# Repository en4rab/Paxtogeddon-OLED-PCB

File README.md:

# Paxtogeddon-OLED-PCB
### Hardware files for the Paxtogeddon reader with OLED display

### kicad

The kicad directory contains the kicad project files to make a PCB for the Paxtogeddon reader. This was a project to learn Kicad and PCB design so set your expectations accordingly! If you just want to make one Paxtogeddon reader to use then you might find using 00Waz's [protoboard design](https://github.com/00Waz/Paxtogeddon-Reader) quicker and easier than ordering pcb's and smt parts from China.

### gerbers

The gerbers directory contains the gerbers for the v1.2 board and a zip file paxtogeddon-gerbers_v1_2.zip which is the zip file uploaded to JLC for manufacture of the PCB's. 

### case

The case directory contains the STL files and parts list for the 3D printed case to suit an Anker 525, 325 or 313 power bank.

### Firmware

This uses mostly the same code written by Daniel as the [board by 00Waz](https://github.com/00Waz/Paxtogeddon-Reader) with some additions to write to an OLED display. However the pin assignments are different and the pins to playback a card are now the same as those used to sniff so the associated headers and transistors can be left off. If this ever gets another revision of the pcb they will be removed. The PaxtogeddonReaderV1 directory contains the first attempt at adding an OLED, the additions were done by en4rab so any mistakes and poor code are my fault and not Daniels!  
[PaxtogeddonReaderV2.2](firmware/PaxtogeddonReaderV2_2) contains Daniel's improved version 2.2 code which supports both this PCB version and the protoboard design by Waz. It uses custom cards to configure the reader. Information on how to rewrite Paxton cards to use as the config cards can be found in [MAKE-CARDS.md](firmware/MAKE-CARDS.md)
This firmware now supports a second esp module connected to the paxtogeddon aux pin to trigger a cheap fitness band to vibrate when a card is read and new with v2.2 support for the paxton hand free interface and hands free fobs.

### Schematic

### Building the PCB
#### Assembly

Assembly is fairly straightforward. When soldering the 4 pin female header for the OLED it is easier to align it if you attach the brass standoffs to an OLED, put the header on the OLED pins then use it as a jig to hold the header in position while you solder it.

The jumper JP1 was for development to allow the 5v to be separated from the ESP32 so the Paxton reader could be powered by 12v while the esp was powered by usb for debugging. In normal use it should be connected.

JP2 and JP3 were to disconnect the card playback pins if that was not needed. In the latest firmware are unused and should be left disconnected.

Once the PCB has been soldered and cleaned use the Halnziye HY910 thermal glue to stick a small aluminium heatsink to the 7805 regulator. Initial tests without a heatsink had the regulator at about 89C adding a small heatsink lowered this to about 75C its a bit of a bodge but it seems to be working ok.

#### Parts used 

This is a list of the parts used. They are not necessarily the best source and if you are being organised you could probably source everything in one order from Mouser/RS/Farnell but the links given are what was used. the 8 way screw terminal was 2x4 way terminals as they were easier to source.

| Reference                     | Value                                                        | Footprint | Link                                                  | Price           |
| ----------------------------- | ------------------------------------------------------------ | --------- | ----------------------------------------------------- | --------------- |
| C1                            | 330nF 50v                                                    | 0805      | https://www.aliexpress.com/item/1005008635911110.html | £12.59 per 2000 |
| C2                            | 1uF 16v                                                      | 0805      | https://www.aliexpress.com/item/33052613891.html      | £0.88 per 100   |
| D1                            | M7 (1N4007)                                                  | A-SMA     | https://www.ebay.co.uk/itm/374441259098               | £4.66 per 100   |
| J1                            | Screw_Terminal_01x02                                         |           | https://www.aliexpress.com/item/1005003556955422.html | £4 per 50       |
| J2                            | 2x Screw_Terminal_01x04                                      |           | https://www.aliexpress.com/item/1005003556955422.html | £7.55 per 50    |
| JP1,JP2,JP3                   | Jumper                                                       |           | https://www.aliexpress.com/item/32853010777.html      | £0.41 per 50    |
| Q1,Q2,Q3,<br />Q4,Q5,Q6       | MMBT3904                                                     | SOT-23    | https://www.aliexpress.com/item/1005006991695298.html | £6.69 per 3000  |
| R1,R2,R3,R4,<br />R5,R6,R7,R8 | 1K 1/4W                                                      | 0805      | https://www.aliexpress.com/item/1005006786740896.html | £5.80 per 5000  |
| U1                            | MC7805CDTG                                                   | TO-252-3  | https://www.aliexpress.com/item/1005007322548974.html | £1.16 per 5     |
| U2                            | ESP32-C3 Supermini                                           |           | https://www.aliexpress.com/item/1005006056663228.html | £1.89           |
| U3                            | OLED096-128x64                                               |           | https://www.aliexpress.com/item/1005006700885056.html | £1.74           |
|                               | 4 pin socket female                                          |           | https://www.ebay.co.uk/itm/192175350096               | £3.89 per 100   |
|                               | Heatsink                                                     | 9x9x5mm   | https://www.aliexpress.com/item/1005004453446730.html | £4.59 per 50    |
|                               | Halnziye HY910<br />Thermal glue                             | 5g        | https://www.ebay.co.uk/itm/256626403139               | £2.75           |
|                               | 11mm M2 brass standoffs and M2 screws to mount the OLED are listed with the case hardware in the case directory |           |                                                       |                 |

> [!CAUTION]
> The ESP32 supermini module has a near identical clone that is badly made and has problems with the wifi, this site describes the issue and how to spot the bad boards [https://roryhay.es/blog/esp32-c3-super-mini-flaw](https://roryhay.es/blog/esp32-c3-super-mini-flaw) TL;DR avoid the boards with "mouse bites" to separate the boards. If you do get a bad board and wifi doesn't work one test board worked better with a small blob of blu-tak stuck on the antenna simulating a finger touching the antenna. Guess how I figured that one out 🤣

> [!WARNING]  
> 0.96" OLED modules come in at least 4 different variants the most significant difference being the order of the pins. This board uses a 4 pin module with GND on the left most pin. They also differ in size and hole spacing. look for a seller showing a board with GME12864-11-12-13 on the back as shown.
>
>   

#### Errata

The latest version of the firmware being developed handles playback differently and doesn't use separate pins. This board used GPIO 20 and 21 for playback and jumpers JP2 and JP3 were to physically disconnect the lines if you didn't want to be able to playback cards. As playback is now done with the same pins as reading they are not used and can be left disconnected.

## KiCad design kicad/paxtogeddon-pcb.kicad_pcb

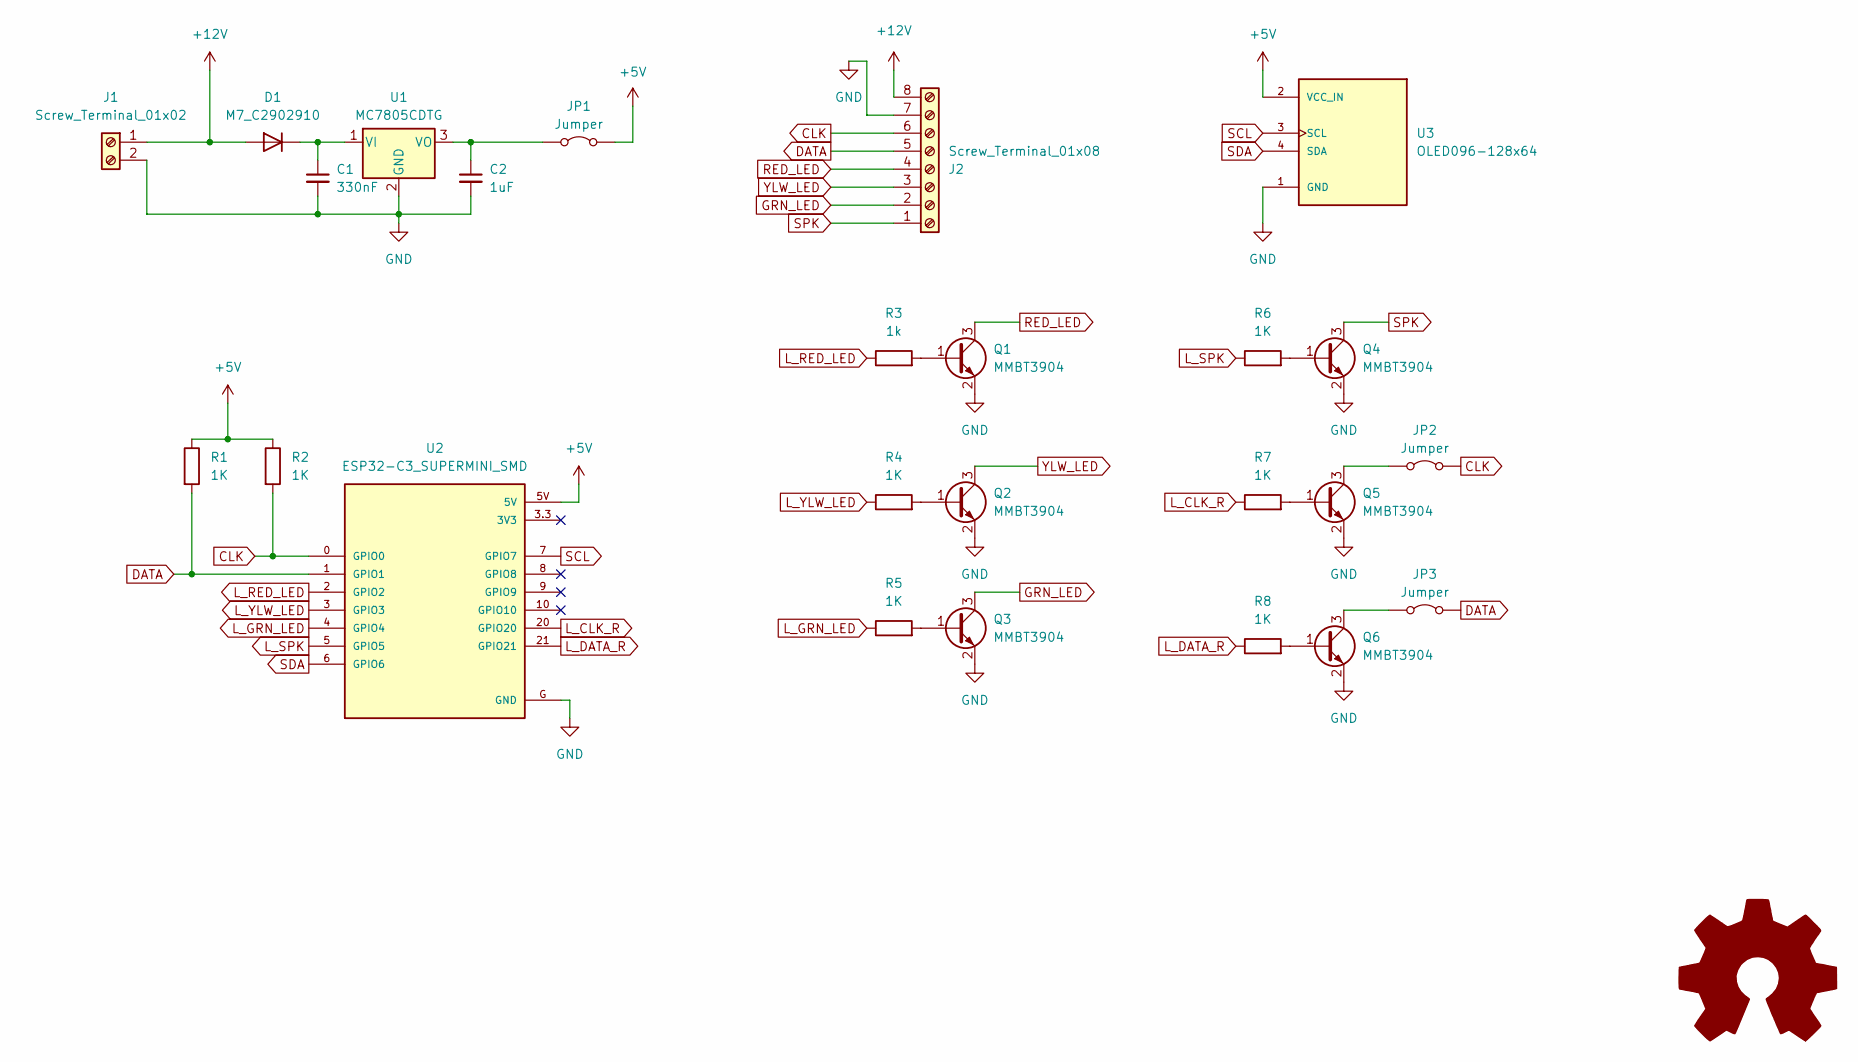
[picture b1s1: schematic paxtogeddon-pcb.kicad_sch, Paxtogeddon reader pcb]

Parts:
C1: 330nF; C_0805_2012Metric_Pad1.18x1.45mm_HandSolder
C2: 1uF; C_0805_2012Metric_Pad1.18x1.45mm_HandSolder
D1: M7_C2902910; D_SMA_Handsoldering
J1: Screw_Terminal_01x02; Altech_AK100_1x02_P5.00mm
J2: Screw_Terminal_01x08; Altech_AK100_1x08_P5.00mm
JP1, JP2, JP3: Jumper; PinHeader_2x01_P2.54mm_Vertical
Q1, Q2, Q3, Q4, Q5, Q6: MMBT3904; SOT-23
R1, R2, R4, R5, R6, R7, R8: 1K; R_0805_2012Metric
R3: 1k; R_0805_2012Metric
U1: MC7805CDTG; TO-252-2
U2: ESP32-C3_SUPERMINI_SMD; MODULE_ESP32-C3_SUPERMINI
U3: OLED096-128x64; MODULE_ER-OLED096-I2C; PARTREV 2018-09-10

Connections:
+5V: JP1.2 (B), R1.1, R2.1, U2.5V, U3.2 (VCC_IN)
+12V: D1.2 (A), J1.1, J2.8
CLK: J2.6, JP2.2 (B), R2.2, U2.0 (GPIO0)
DATA: J2.5, JP3.2 (B), R1.2, U2.1 (GPIO1)
GND: C1.2, C2.2, J1.2, J2.7, Q1.2 (E), Q2.2 (E), Q3.2 (E), Q4.2 (E), Q5.2 (E), Q6.2 (E), U1.2 (GND), U2.G (GND), U3.1 (GND)
GRN_LED: J2.2, Q3.3 (C)
L_CLK_R: R7.1, U2.20 (GPIO20)
L_DATA_R: R8.1, U2.21 (GPIO21)
L_GRN_LED: R5.1, U2.4 (GPIO4)
L_RED_LED: R3.1, U2.2 (GPIO2)
L_SPK: R6.1, U2.5 (GPIO5)
L_YLW_LED: R4.1, U2.3 (GPIO3)
unnamed: C1.1, D1.1 (K), U1.1 (VI)
unnamed: C2.1, JP1.1 (A), U1.3 (VO)
unnamed: JP2.1 (A), Q5.3 (C)
unnamed: JP3.1 (A), Q6.3 (C)
unnamed: Q1.1 (B), R3.2
unnamed: Q2.1 (B), R4.2
unnamed: Q3.1 (B), R5.2
unnamed: Q4.1 (B), R6.2
unnamed: Q5.1 (B), R7.2
unnamed: Q6.1 (B), R8.2
RED_LED: J2.4, Q1.3 (C)
SCL: U2.7 (GPIO7), U3.3 (SCL)
SDA: U2.6 (GPIO6), U3.4 (SDA)
SPK: J2.1, Q4.3 (C)
YLW_LED: J2.3, Q2.3 (C)

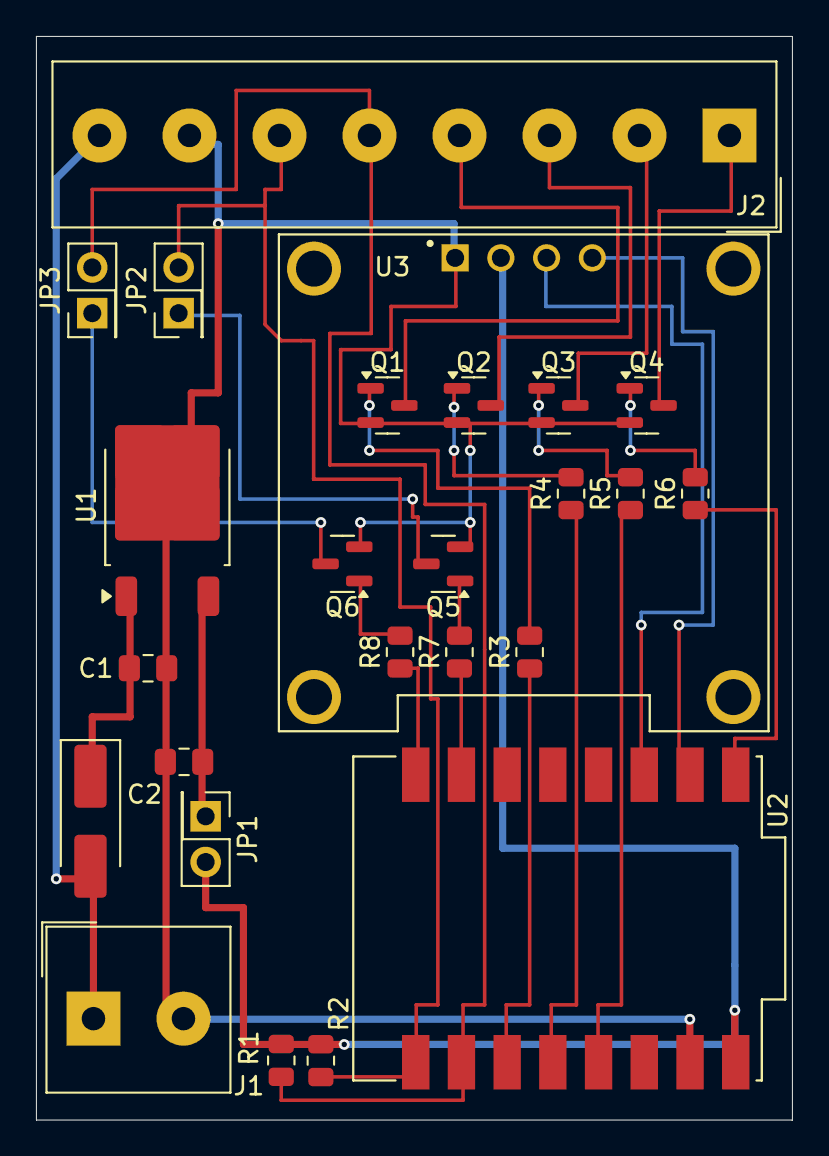
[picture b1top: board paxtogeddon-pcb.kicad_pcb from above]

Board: 2 copper layers, 42.0 x 60.2 mm, 25 parts (0 on the bottom side), 27 nets.

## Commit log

2025-06-10 Initial commit
    Initial commit
2025-06-10 Update README.md
    Inevitable mistakes fixed
2025-06-10 Add front view of bracket
    Add front view of bracket assembly
2025-06-10 Update README.md
    Typos
2025-06-10 Add V1 firmware
    Add V1 firmware as placeholder until V2 is finalised
2025-06-10 Add warnings about ESP32 and OLED sourcing
2025-06-27 Add Daniels V2 firmware
    Add the source for Daniels V2 firmware and windows companion app
2025-06-29 Update README.md
    Add info on Anker 525 end of production
2025-07-09 Add anker 313 infill STL
    Add STL for Anker 313 powerbank adapter
2025-07-14 Update documentation
    Update documentation to add config card info and remove PD module info from parts list
2025-07-14 Update MAKE-CARDS.md
    fix formatting of code blocks
2025-07-14 Rename firmware folders
    Rename firmware folders so the sketch name matches the folder name
2025-07-14 Update README.md
    Fix heading sizes
2025-07-14 Update README.md
    fix link to firmware
2025-07-18 Add info on programming config cards
2025-07-18 Update screenshots
2025-08-02 Add info on reader ferrules
2025-08-04 Update README.md
    Update that replay pins nolonger needed
2025-11-10 Initial add of V2.1 firmware
    Add V2.1 of the firmware which adds support for vibrating a BLE band
2026-01-30 Update firmware to V2.2
    Add version 2.2 firmware with support for hands free interface/fob
2026-01-30 update latest version in readme
2026-02-18 Add V2.3 firmware
    Add version 2.3 firmware
2026-02-26 Add V2.4 firmware
    Add the latest V2.4 firmware
2026-04-10 Add initial BLE integration code
    Add support for vibrating a miband when card is read for haptic feedback
2026-04-10 Get and save ble address type from band
